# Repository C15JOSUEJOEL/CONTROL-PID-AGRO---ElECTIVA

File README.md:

# CONTROL-PID-AGRO---ELECTIVA
Grupo para CONTROL PID (AGRO)
===============================================================================================
Perspectiva del producto
===============================================================================================
El proyecto se plantea como una herramienta didáctica para facilitar la enseñanza y aplicación práctica del control PID. Su uso principal será en laboratorios de mecatrónica y sistemas de control, donde estudiantes y profesores podrán experimentar con la estabilización de sistemas. Además, se busca que sea portátil, mantenible y adaptable a futuras aplicaciones educativas.

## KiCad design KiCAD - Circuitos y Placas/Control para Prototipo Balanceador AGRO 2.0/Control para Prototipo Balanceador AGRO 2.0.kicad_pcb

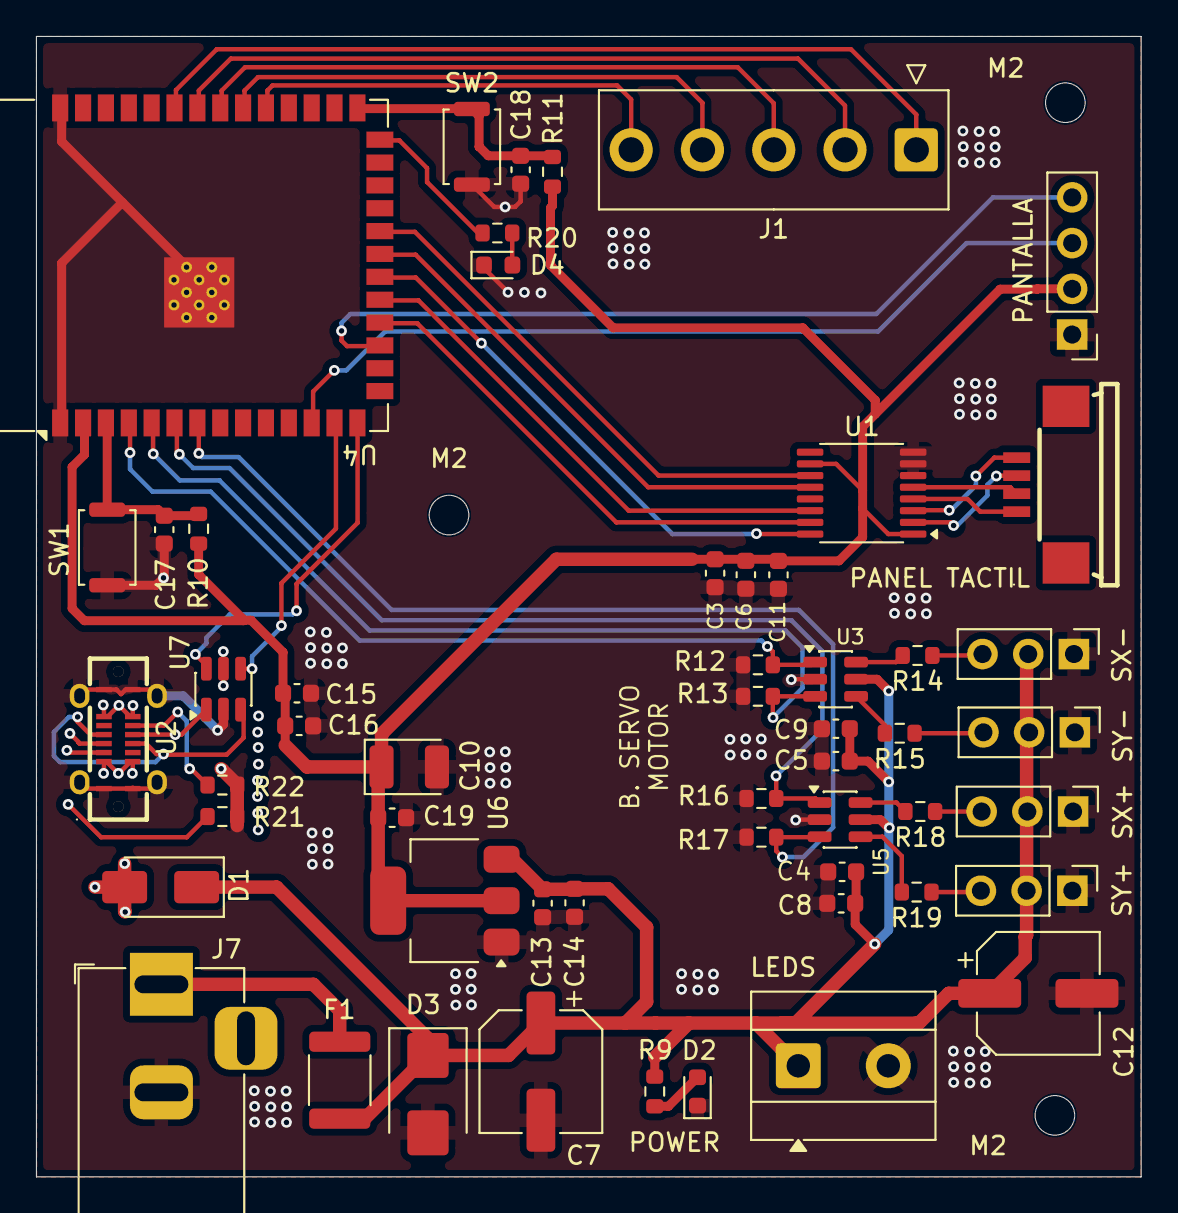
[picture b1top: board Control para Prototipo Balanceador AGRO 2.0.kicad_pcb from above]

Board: 4 copper layers, 61.4 x 63.4 mm, 57 parts (0 on the bottom side), 44 nets.

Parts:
C3, C8, C9, C11, C15: 0.1uF; C_0603_1608Metric
C4, C5, C6, C16: 10uF; C_0603_1608Metric
C7: 220uF; CP_Elec_6.3x7.7
C10: 22uF; CP_EIA-3528-21_Kemet-B
C12: 470uF; CP_Elec_6.3x7.7
C13: 22uF; C_0603_1608Metric
C14, C19: 0.1uf; C_0603_1608Metric
C17, C18: 1uF; C_0603_1608Metric
D1: D_Schottky; D_SMA
D2, D4: LED; LED_0603_1608Metric
D3: SM6T6V8A; D_SMB
F1: 5A; Fuse_1812_4532Metric
J1: Conexiones_adicionales; TE_826576-5_1x05_P3.96mm_Vertical
J7: 5V 15A; BarrelJack_Horizontal
LEDS: LEDS; TerminalBlock_MetzConnect_Type055_RT01502HDWU_1x02_P5.00mm_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
M2, M2#2, M2#3: MountingHole_2.2mm_M2
PANEL TACTIL: 1.0K-ES-4PWB-RL; C51901481_FPC-SMD_4P-P1_00_1_0K-ES-4PWB-RL
PANTALLA: Conn_01x04_Pin; PinHeader_1x04_P2.54mm_Vertical
R9, R14, R15, R18, R19, R20: 220; R_0603_1608Metric
R10, R11, R12, R13, R16, R17: 10K; R_0603_1608Metric
R21, R22: 5,1k; R_0603_1608Metric
SW1, SW2: SW_Push; SW_Push_SPST_NO_Alps_SKRK
SX+: Conector_X; PinHeader_1x03_P2.54mm_Vertical
SX-: Conector_X; PinHeader_1x03_P2.54mm_Vertical
SY+: Conector_Y; PinHeader_1x03_P2.54mm_Vertical
SY-: Conector_Y; PinHeader_1x03_P2.54mm_Vertical
U1: TSC2046IPW; TSSOP-16_4.4x5mm_P0.65mm
U2: TYPE-C 16PLT-H10.0; C3151749_TYPE-C-SMD_USB4120-03-C
U3, U5: 74HCT2G34; SOT-23-6
U4: ESP32-S3-WROOM-1
U6: AMS1117-3.3; SOT-223-3_TabPin2
U7: USBLC6-2SC6; SOT-23-6

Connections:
+3.3V: C3.1, C6.1, C10.1, C11.1, C15.1, C16.1, C19.1, PANTALLA.2, R10.1, R11.1, U1.1 (VCC+), U1.10 (IOVDD), U4.2 (3V3), U6.2 (VO)
+5V: C4.1, C5.1, C7.1, C8.1, C9.1, C12.1, C13.1, C14.1, D1.1 (K), D3.1 (A1), F1.1, LEDS.1, R9.2, SX+.2, SX-.2, SY+.2, SY-.2, U3.5 (VCC), U5.5 (VCC), U6.3 (VI)
/USB_DN: U4.13 (USB_D-), U7.4 (I/O2)
/USB_DP: U4.14 (USB_D+), U7.6 (I/O1)
CHIP_1A: R12.2, U3.1 (1A), U4.4 (IO4)
CHIP_2A: R13.2, U3.3 (2A), U4.5 (IO5)
CHIP_3A: R16.2, U4.6 (IO6), U5.1 (1A)
CHIP_4A: R17.2, U4.7 (IO7), U5.3 (2A)
DN_1Y2: U2.A7 (DN1), U2.B7 (DN2), U7.3 (I/O2)
DP_1Y2: U2.A6 (DP1), U2.B6 (DP2), U7.1 (I/O1)
ESP_EN: C17.2, R10.2, SW1.1, U4.3 (EN)
ESP_IO0: C18.1, R11.2, SW2.1, U4.27 (IO0)
GND: C3.2, C4.2, C5.2, C6.2, C7.2, C8.2, C9.2, C10.2, C11.2, C12.2, C13.2, C14.2, C15.2, C16.2, C17.1, C18.2, C19.2, D2.1 (K), D3.2 (A2), D4.1 (K), J7.2, LEDS.2, PANTALLA.1, R12.1, R13.1, R16.1, R17.1, R21.2, R22.1, SW1.2, SW2.2, SX+.1, SX-.1, SY+.1, SY-.1, U1.6 (GND), U1.7 (VBAT), U1.8 (AUX), U2.0 (EH), U2.A1 (GND), U2.A12 (GND), U2.B1 (GND), U2.B12 (GND), U3.2 (GND), U4.1 (GND), U4.40 (GND), U4.41 (GND), U5.2 (GND), U6.1 (GND), U7.2 (GND)
I2C_SCL: PANTALLA.4, U4.17 (IO9)
I2C_SDA: PANTALLA.3, U4.12 (IO8)
MISO: U1.12 (DOUT), U4.21 (IO13)
MOSI: U1.14 (DIN), U4.19 (IO11)
unnamed: D2.2 (A), R9.1
unnamed: D4.2 (A), R20.1
unnamed: F1.2, J7.1
unnamed: J1.1, U4.35 (IO42)
unnamed: J1.2, U4.34 (IO41)
unnamed: J1.3, U4.33 (IO40)
unnamed: J1.4, U4.32 (IO39)
unnamed: J1.5, U4.31 (IO38)
unnamed: R21.1, U2.A5 (CC1)
unnamed: R22.2, U2.B5 (CC2)
unnamed: R14.2, U3.6 (1Y)
unnamed: R15.2, U3.4 (2Y)
unnamed: R20.2, U4.26 (IO45)
unnamed: R18.2, U5.6 (1Y)
unnamed: R19.2, U5.4 (2Y)
SCK: U1.16 (DCLK), U4.20 (IO12)
Servo_Motor_XN_Signal: R14.1, SX-.3
Servo_Motor_XP_Signal: R18.1, SX+.3
Servo_Motor_YN_Signal: R15.1, SY-.3
Servo_Motor_YP_Signal: R19.1, SY+.3
TP_CS: U1.15 (*CS), U4.18 (IO10)
TP_IRQ: U1.11 (*PENIRQ), U4.22 (IO14)
VBUS: D1.2 (A), U2.A4 (VBUS), U2.A9 (VBUS), U2.B4 (VBUS), U2.B9 (VBUS), U7.5 (VBUS)
X+: PANEL TACTIL.3, U1.2 (X+)
X-: PANEL TACTIL.1, U1.4 (X-)
Y+: PANEL TACTIL.4, U1.3 (Y+)
Y-: PANEL TACTIL.2, U1.5 (Y-)

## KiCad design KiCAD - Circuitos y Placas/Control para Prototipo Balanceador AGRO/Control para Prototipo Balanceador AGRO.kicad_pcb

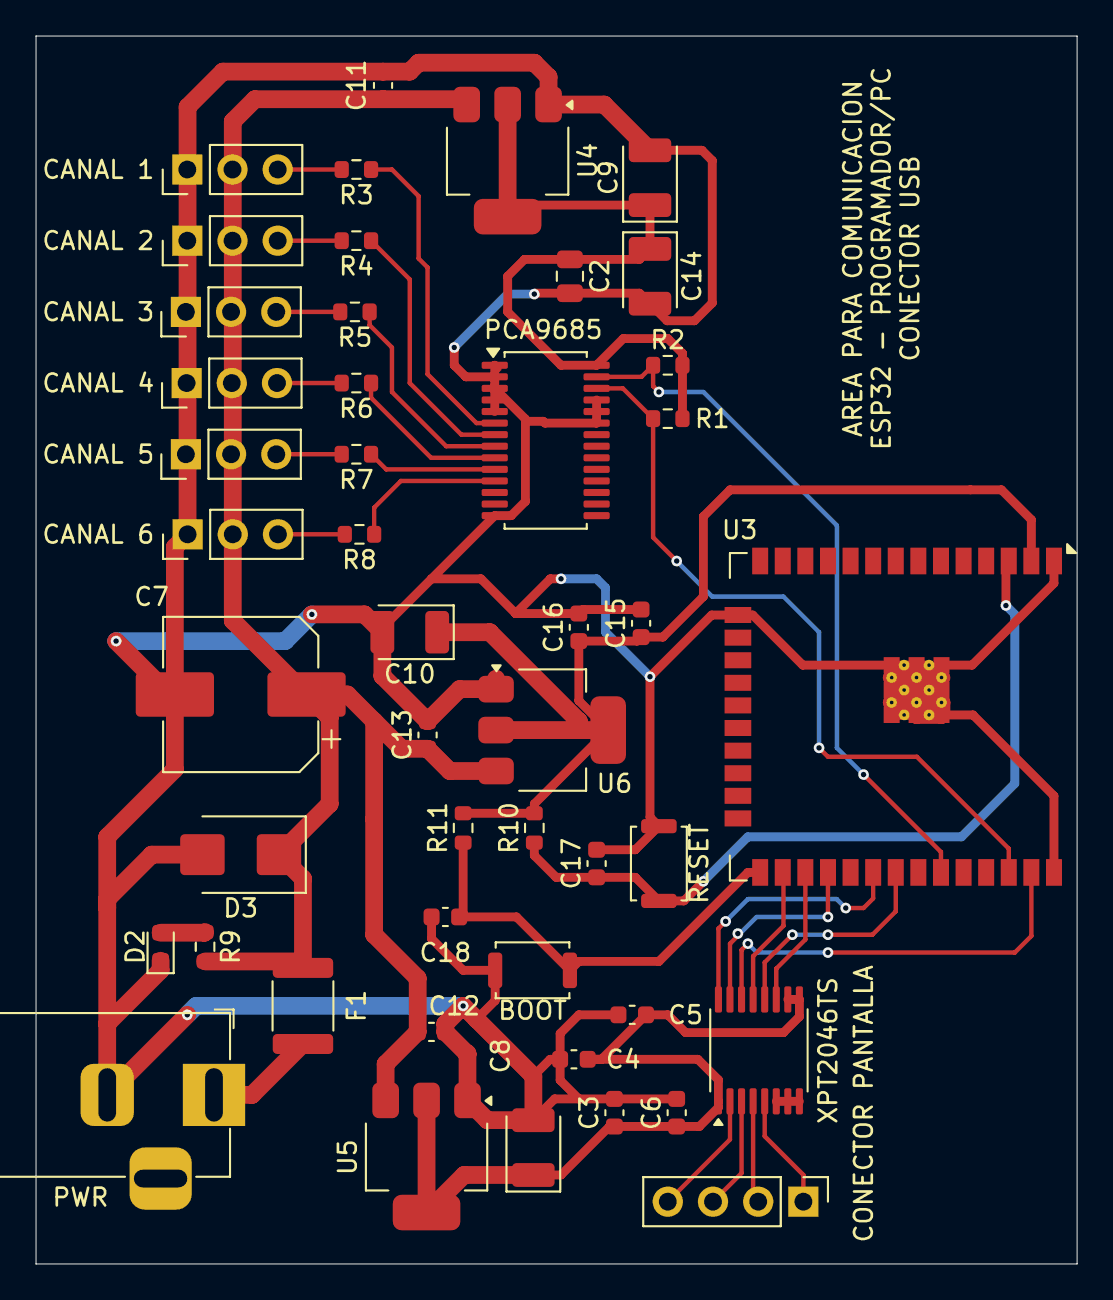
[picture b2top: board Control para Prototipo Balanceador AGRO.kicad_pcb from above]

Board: 2 copper layers, 58.5 x 69.0 mm, 47 parts (0 on the bottom side), 33 nets.

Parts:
BOOT: SW_Push; SW_Push_SPST_NO_Alps_SKRK
C2: 10uF; C_0805_2012Metric
C3, C4, C5, C6, C15, C17, C18: 0.1uF; C_0603_1608Metric
C7: 1000uF; CP_Elec_8x10.5
C8, C9, C10: 22uF; CP_EIA-3528-12_Kemet-T
C11, C12, C13: 22uF; C_0603_1608Metric
C14: 100uF; CP_EIA-3528-12_Kemet-T
C16: 10uF; C_0603_1608Metric
CANAL 1, CANAL 2, CANAL 3, CANAL 4, CANAL 5, CANAL 6: Conn_01x03_Pin; PinHeader_1x03_P2.54mm_Vertical
CONECTOR PANTALLA: Conn_01x04_Pin; PinHeader_1x04_P2.54mm_Vertical
D2: LED; LED_0603_1608Metric
D3: SM6T6V8A; D_SMB
F1: 5A; Fuse_1812_4532Metric
PCA9685: PCA9685PW; TSSOP-28_4.4x9.7mm_P0.65mm
PWR: 5V_15A; BarrelJack_Horizontal
R1, R2: 4.7k; R_0603_1608Metric
R3, R4, R5, R6, R7, R8: 220; R_0603_1608Metric
R9: 1k; R_0603_1608Metric
R10, R11: 10K; R_0603_1608Metric
RESET: SW_Push; SW_Push_SPST_NO_Alps_SKRK
U3: ESP32-WROOM-32E
U4, U5, U6: AMS1117-3.3; SOT-223-3_TabPin2
XPT2046TS: XPT2046TS; TSSOP-16_4.4x5mm_P0.65mm

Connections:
+5V: C7.1, C11.1, C12.1, C13.1, CANAL 1.2, CANAL 2.2, CANAL 3.2, CANAL 4.2, CANAL 5.2, CANAL 6.2, D3.1 (A1), F1.1, R9.2, U4.3 (VI), U5.3 (VI), U6.3 (VI)
GND: BOOT.2, C2.2, C3.2, C4.2, C5.2, C6.2, C7.2, C8.2, C9.2, C10.2, C11.2, C12.2, C13.2, C14.2, C15.2, C16.2, C17.2, C18.2, CANAL 1.1, CANAL 2.1, CANAL 3.1, CANAL 4.1, CANAL 5.1, CANAL 6.1, D2.1 (K), D3.2 (A2), PCA9685.1 (A0), PCA9685.2 (A1), PCA9685.3 (A2), PCA9685.4 (A3), PCA9685.5 (A4), PCA9685.14 (VSS), PCA9685.23 (~OE), PCA9685.24 (A5), PCA9685.25 (EXTCLK), PWR.2, RESET.1, U3.1 (GND), U3.15 (GND), U3.38 (GND), U3.39 (GND), U4.1 (GND), U5.1 (GND), U6.1 (GND), XPT2046TS.6 (GND), XPT2046TS.7 (VBAT), XPT2046TS.8 (IN)
I2C_SCL: PCA9685.26 (SCL), R1.1, U3.36 (IO22)
I2C_SDA: PCA9685.27 (SDA), R2.1, U3.33 (IO21)
MISO: U3.31 (IO19), XPT2046TS.12 (DOUT)
MOSI: U3.37 (IO23), XPT2046TS.14 (DIN)
unnamed: D2.2 (A), R9.1
unnamed: F1.2, PWR.1
unnamed: PCA9685.6 (LED0), R3.1
unnamed: PCA9685.7 (LED1), R4.1
unnamed: PCA9685.8 (LED2), R5.1
unnamed: PCA9685.9 (LED3), R6.1
unnamed: PCA9685.10 (LED4), R7.1
unnamed: PCA9685.11 (LED5), R8.1
unnamed: C17.1, R10.1, RESET.2, U3.3 (EN)
unnamed: BOOT.1, C18.1, R11.1, U3.25 (IO0)
POWER_C_SERVO_3.3V: C2.1, C9.1, C14.1, PCA9685.28 (VDD), R1.2, R2.2, U4.2 (VO)
POWER_ESP32_3.3V: C10.1, C15.1, C16.1, R10.2, R11.2, U3.2 (VDD), U6.2 (VO)
POWER_SCREEN_3.3V: C3.1, C4.1, C5.1, C6.1, C8.1, U5.2 (VO), XPT2046TS.1 (VCC), XPT2046TS.9 (VREF), XPT2046TS.10 (IOVDD)
SCK: U3.30 (IO18), XPT2046TS.16 (DCLK)
SERVO1_SIG: CANAL 1.3, R3.2
SERVO2_SIG: CANAL 2.3, R4.2
SERVO3_SIG: CANAL 3.3, R5.2
SERVO4_SIG: CANAL 4.3, R6.2
SERVO5_SIG: CANAL 5.3, R7.2
SERVO6_SIG: CANAL 6.3, R8.2
TP_BUSY: U3.26 (IO4), XPT2046TS.13 (BUSY)
TP_CS: U3.28 (IO17), XPT2046TS.15 (~CS)
TP_IRQ: U3.27 (IO16), XPT2046TS.11 (~PENIRQ)
X+: CONECTOR PANTALLA.4, XPT2046TS.2 (XP)
X-: CONECTOR PANTALLA.2, XPT2046TS.4 (XN)
Y+: CONECTOR PANTALLA.3, XPT2046TS.3 (YP)
Y-: CONECTOR PANTALLA.1, XPT2046TS.5 (YN)
